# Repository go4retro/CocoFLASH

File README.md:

# CocoFLASH
Tandy Color Computer CocoFLASH

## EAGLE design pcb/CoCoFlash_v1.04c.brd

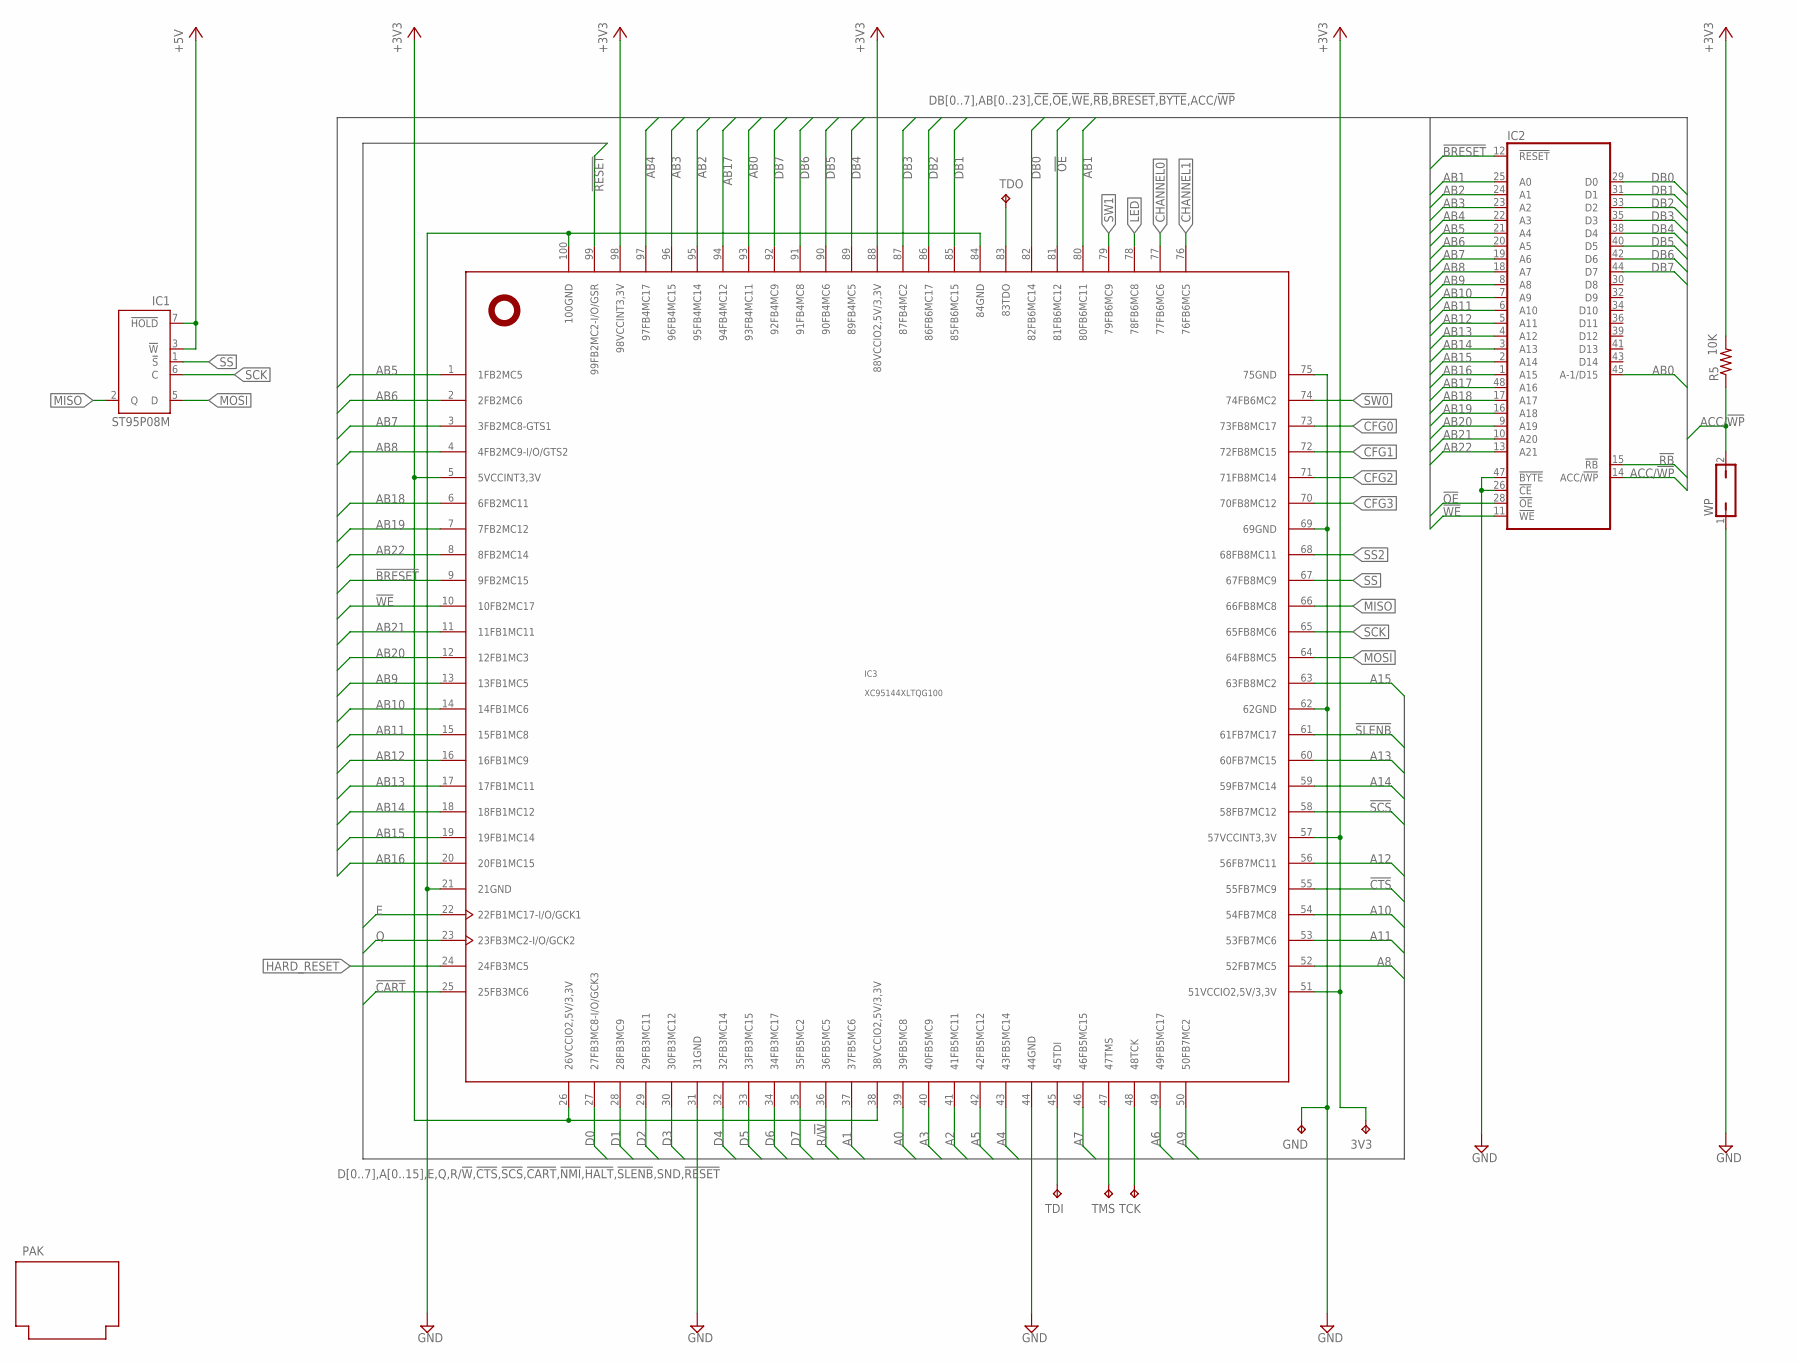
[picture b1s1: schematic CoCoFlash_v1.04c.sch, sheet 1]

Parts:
3V3: TPTP08R; TP08R
GND: TPTP08R; TP08R
IC1: ST95P08M; SO08
IC2: MX29LV640; TSOP48
IC3: XC95144XLTQG100; TQFP100
PAK: PROGRAM_PAK
R5: 10K; R0402
TCK: TPTP08R; TP08R
TDI: TPTP08R; TP08R
TDO: TPTP08R; TP08R
TMS: TPTP08R; TP08R
WP: JP1Q; JP1

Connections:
!BRESET: IC2.12 (!RESET), IC3.9 (9FB2MC15)
!CART: IC3.25 (25FB3MC6); also elsewhere on the board
!CTS: IC3.55 (55FB7MC9); also elsewhere on the board
!OE: IC2.28 (!OE), IC3.81 (81FB6MC12)
!RB: IC2.15 (!RB)
!RESET: IC3.99 (99FB2MC2-I/O/GSR); also elsewhere on the board
!SCS: IC3.58 (58FB7MC12); also elsewhere on the board
!SLENB: IC3.61 (61FB7MC17); also elsewhere on the board
!WE: IC2.11 (!WE), IC3.10 (10FB2MC17)
+3V3: 3V3.TP, IC3.5 (5VCCINT3,3V), IC3.26 (26VCCIO2,5V/3,3V), IC3.38 (38VCCIO2,5V/3,3V), IC3.51 (51VCCIO2,5V/3,3V), IC3.57 (57VCCINT3,3V), IC3.88 (88VCCIO2,5V/3,3V), IC3.98 (98VCCINT3,3V), R5.2; also elsewhere on the board
+5V: IC1.3 (!W), IC1.7 (!HOLD); also elsewhere on the board
A0: IC3.39 (39FB5MC8); also elsewhere on the board
A1: IC3.37 (37FB5MC6); also elsewhere on the board
A2: IC3.41 (41FB5MC11); also elsewhere on the board
A3: IC3.40 (40FB5MC9); also elsewhere on the board
A4: IC3.43 (43FB5MC14); also elsewhere on the board
A5: IC3.42 (42FB5MC12); also elsewhere on the board
A6: IC3.49 (49FB5MC17); also elsewhere on the board
A7: IC3.46 (46FB5MC15); also elsewhere on the board
A8: IC3.52 (52FB7MC5); also elsewhere on the board
A9: IC3.50 (50FB7MC2); also elsewhere on the board
A10: IC3.54 (54FB7MC8); also elsewhere on the board
A11: IC3.53 (53FB7MC6); also elsewhere on the board
A12: IC3.56 (56FB7MC11); also elsewhere on the board
A13: IC3.60 (60FB7MC15); also elsewhere on the board
A14: IC3.59 (59FB7MC14); also elsewhere on the board
A15: IC3.63 (63FB8MC2); also elsewhere on the board
AB0: IC2.45 (A-1/D15), IC3.93 (93FB4MC11)
AB1: IC2.25 (A0), IC3.80 (80FB6MC11)
AB2: IC2.24 (A1), IC3.95 (95FB4MC14)
AB3: IC2.23 (A2), IC3.96 (96FB4MC15)
AB4: IC2.22 (A3), IC3.97 (97FB4MC17)
AB5: IC2.21 (A4), IC3.1 (1FB2MC5)
AB6: IC2.20 (A5), IC3.2 (2FB2MC6)
AB7: IC2.19 (A6), IC3.3 (3FB2MC8-GTS1)
AB8: IC2.18 (A7), IC3.4 (4FB2MC9-I/O/GTS2)
AB9: IC2.8 (A8), IC3.13 (13FB1MC5)
AB10: IC2.7 (A9), IC3.14 (14FB1MC6)
AB11: IC2.6 (A10), IC3.15 (15FB1MC8)
AB12: IC2.5 (A11), IC3.16 (16FB1MC9)
AB13: IC2.4 (A12), IC3.17 (17FB1MC11)
AB14: IC2.3 (A13), IC3.18 (18FB1MC12)
AB15: IC2.2 (A14), IC3.19 (19FB1MC14)
AB16: IC2.1 (A15), IC3.20 (20FB1MC15)
AB17: IC2.48 (A16), IC3.94 (94FB4MC12)
AB18: IC2.17 (A17), IC3.6 (6FB2MC11)
AB19: IC2.16 (A18), IC3.7 (7FB2MC12)
AB20: IC2.9 (A19), IC3.12 (12FB1MC3)
AB21: IC2.10 (A20), IC3.11 (11FB1MC11)
AB22: IC2.13 (A21), IC3.8 (8FB2MC14)
ACC/!WP: IC2.14 (ACC/!WP), R5.1, WP.2
CFG0: IC3.73 (73FB8MC17); also elsewhere on the board
CFG1: IC3.72 (72FB8MC15); also elsewhere on the board
CFG2: IC3.71 (71FB8MC14); also elsewhere on the board
CFG3: IC3.70 (70FB8MC12); also elsewhere on the board
CHANNEL0: IC3.77 (77FB6MC6); also elsewhere on the board
CHANNEL1: IC3.76 (76FB6MC5); also elsewhere on the board
D0: IC3.27 (27FB3MC8-I/O/GCK3); also elsewhere on the board
D1: IC3.28 (28FB3MC9); also elsewhere on the board
D2: IC3.29 (29FB3MC11); also elsewhere on the board
D3: IC3.30 (30FB3MC12); also elsewhere on the board
D4: IC3.32 (32FB3MC14); also elsewhere on the board
D5: IC3.33 (33FB3MC15); also elsewhere on the board
D6: IC3.34 (34FB3MC17); also elsewhere on the board
D7: IC3.35 (35FB5MC2); also elsewhere on the board
DB0: IC2.29 (D0), IC3.82 (82FB6MC14)
DB1: IC2.31 (D1), IC3.85 (85FB6MC15)
DB2: IC2.33 (D2), IC3.86 (86FB6MC17)
DB3: IC2.35 (D3), IC3.87 (87FB4MC2)
DB4: IC2.38 (D4), IC3.89 (89FB4MC5)
DB5: IC2.40 (D5), IC3.90 (90FB4MC6)
DB6: IC2.42 (D6), IC3.91 (91FB4MC8)
DB7: IC2.44 (D7), IC3.92 (92FB4MC9)
E: IC3.22 (22FB1MC17-I/O/GCK1); also elsewhere on the board
GND: GND.TP, IC2.26 (!CE), IC2.47 (!BYTE), IC3.21 (21GND), IC3.31 (31GND), IC3.44 (44GND), IC3.62 (62GND), IC3.69 (69GND), IC3.75 (75GND), IC3.84 (84GND), IC3.100 (100GND), WP.1; also elsewhere on the board
HARD_RESET: IC3.24 (24FB3MC5); also elsewhere on the board
LED: IC3.78 (78FB6MC8); also elsewhere on the board
MISO: IC1.2 (Q), IC3.66 (66FB8MC8)
MOSI: IC1.5 (D), IC3.64 (64FB8MC5)
unnamed: IC3.45 (45TDI), TDI.TP
unnamed: IC3.47 (47TMS), TMS.TP
unnamed: IC3.48 (48TCK), TCK.TP
unnamed: IC3.83 (83TDO), TDO.TP
Q: IC3.23 (23FB3MC2-I/O/GCK2); also elsewhere on the board
R/!W: IC3.36 (36FB5MC5); also elsewhere on the board
SCK: IC1.6 (C), IC3.65 (65FB8MC6)
SS: IC1.1 (!S), IC3.67 (67FB8MC9)
SS2: IC3.68 (68FB8MC11)
SW0: IC3.74 (74FB6MC2); also elsewhere on the board
SW1: IC3.79 (79FB6MC9); also elsewhere on the board

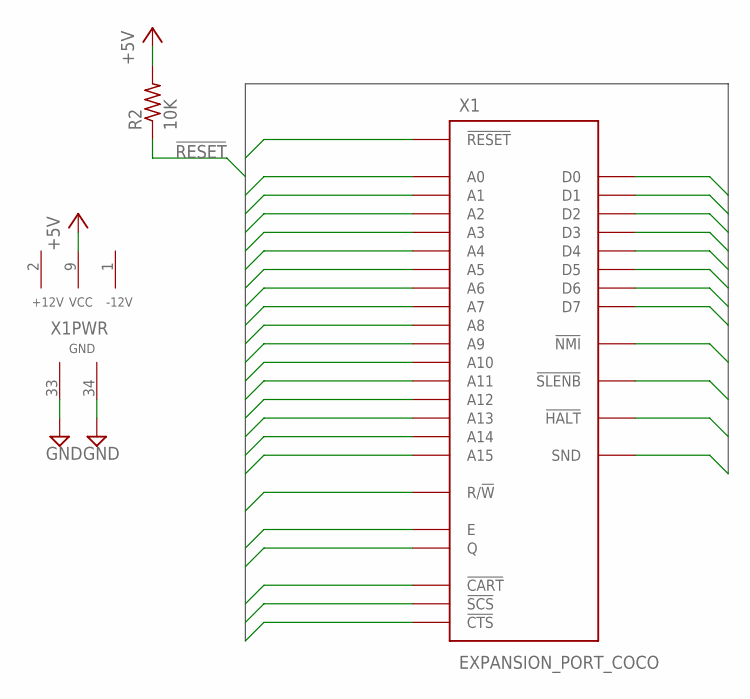
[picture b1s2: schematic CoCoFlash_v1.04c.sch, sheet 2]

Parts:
R2: 10K; R0402
X1: EXPANSION_PORT_COCO; MA20-2

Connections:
!CART: X1.8 (!CART); also elsewhere on the board
!CTS: X1.32 (!CTS); also elsewhere on the board
!HALT: X1.3 (!HALT)
!NMI: X1.4 (!NMI)
!RESET: R2.1, X1.5 (!RESET); also elsewhere on the board
!SCS: X1.36 (!SCS); also elsewhere on the board
!SLENB: X1.40 (!SLENB); also elsewhere on the board
+5V: R2.2, X1.9 (VCC); also elsewhere on the board
+12V: X1.2 (+12V)
-12V: X1.1 (-12V)
A0: X1.19 (A0); also elsewhere on the board
A1: X1.20 (A1); also elsewhere on the board
A2: X1.21 (A2); also elsewhere on the board
A3: X1.22 (A3); also elsewhere on the board
A4: X1.23 (A4); also elsewhere on the board
A5: X1.24 (A5); also elsewhere on the board
A6: X1.25 (A6); also elsewhere on the board
A7: X1.26 (A7); also elsewhere on the board
A8: X1.27 (A8); also elsewhere on the board
A9: X1.28 (A9); also elsewhere on the board
A10: X1.29 (A10); also elsewhere on the board
A11: X1.30 (A11); also elsewhere on the board
A12: X1.31 (A12); also elsewhere on the board
A13: X1.37 (A13); also elsewhere on the board
A14: X1.38 (A14); also elsewhere on the board
A15: X1.39 (A15); also elsewhere on the board
D0: X1.10 (D0); also elsewhere on the board
D1: X1.11 (D1); also elsewhere on the board
D2: X1.12 (D2); also elsewhere on the board
D3: X1.13 (D3); also elsewhere on the board
D4: X1.14 (D4); also elsewhere on the board
D5: X1.15 (D5); also elsewhere on the board
D6: X1.16 (D6); also elsewhere on the board
D7: X1.17 (D7); also elsewhere on the board
E: X1.6 (E); also elsewhere on the board
GND: X1.33 (GND), X1.34 (GND); also elsewhere on the board
Q: X1.7 (Q); also elsewhere on the board
R/!W: X1.18 (R/!W); also elsewhere on the board
SND: X1.35 (SND); also elsewhere on the board

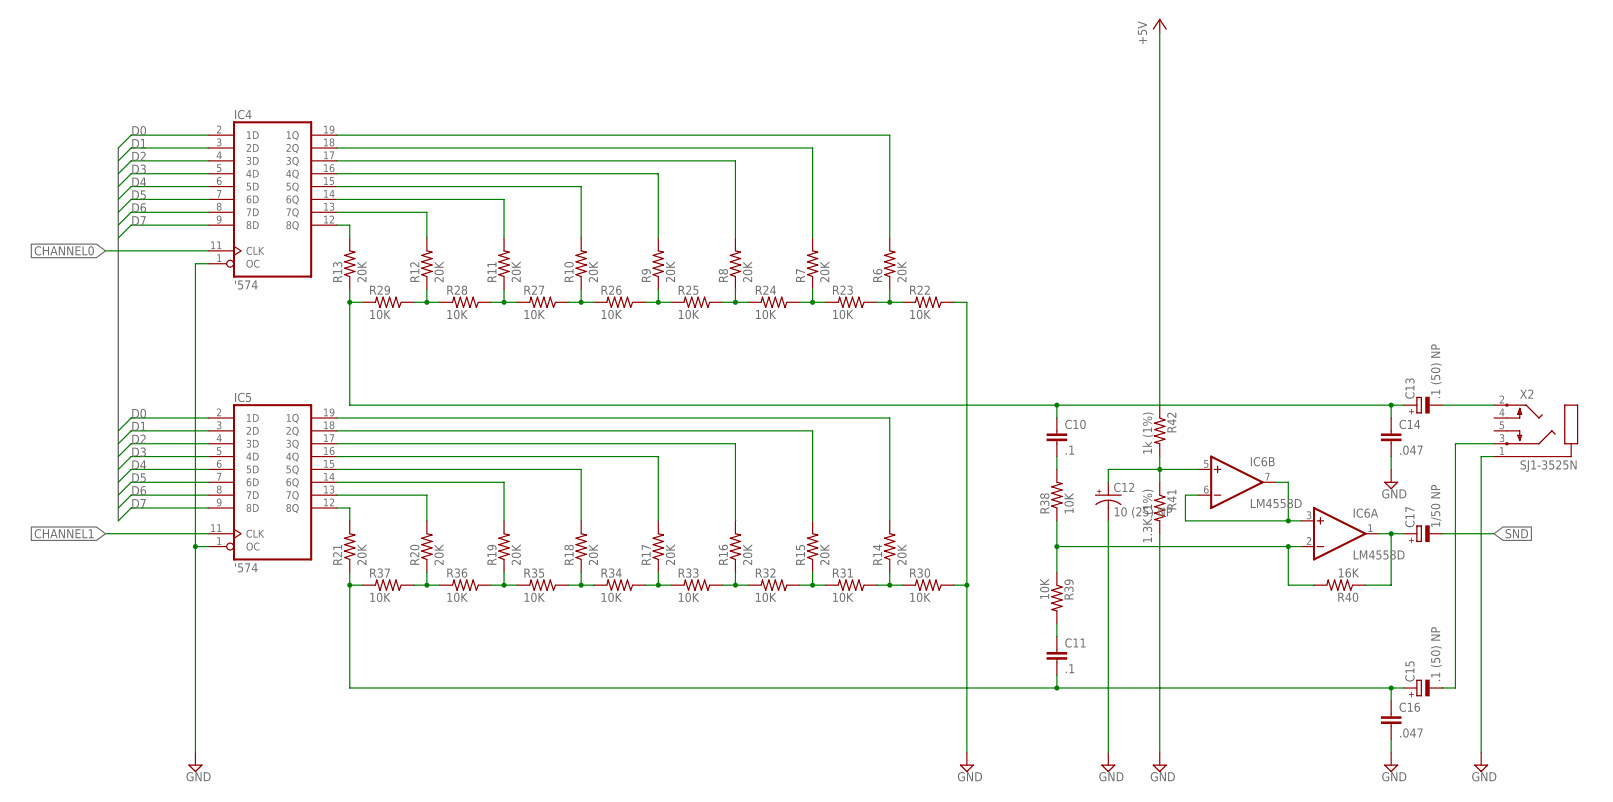
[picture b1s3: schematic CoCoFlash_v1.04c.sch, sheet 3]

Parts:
C10, C11: .1; C050-025X075
C12: 10 (25) NP; E1,8-4
C13, C15: .1 (50) NP; E1,8-4
C14, C16: .047; C050-025X075
C17: 1/50 NP; E1,8-4
IC4, IC5: '574; TSSOP20
IC6: LM4558D; SO08
R6, R7, R8, R9, R10, R11, R12, R13, R14, R15, R16, R17, R18, R19, R20, R21: 20K; R1206
R22, R23, R24, R25, R26, R27, R28, R29, R30, R31, R32, R33, R34, R35, R36, R37, R38, R39: 10K; R1206
R40: 16K; R1206
R41: 1.3K (1%); R0402
R42: 1k (1%); R0402
X2: SJ1-3525N

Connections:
+5V: R42.1; also elsewhere on the board
CHANNEL0: IC4.11 (CLK); also elsewhere on the board
CHANNEL1: IC5.11 (CLK); also elsewhere on the board
D0: IC4.2 (1D), IC5.2 (1D); also elsewhere on the board
D1: IC4.3 (2D), IC5.3 (2D); also elsewhere on the board
D2: IC4.4 (3D), IC5.4 (3D); also elsewhere on the board
D3: IC4.5 (4D), IC5.5 (4D); also elsewhere on the board
D4: IC4.6 (5D), IC5.6 (5D); also elsewhere on the board
D5: IC4.7 (6D), IC5.7 (6D); also elsewhere on the board
D6: IC4.8 (7D), IC5.8 (7D); also elsewhere on the board
D7: IC4.9 (8D), IC5.9 (8D); also elsewhere on the board
GND: C12.-, C14.2, C16.2, IC4.1 (OC), IC5.1 (OC), R22.1, R30.1, R41.2, X2.1; also elsewhere on the board
unnamed: IC4.18 (2Q), R7.2
unnamed: R6.1, R22.2, R23.1
unnamed: C15.-, X2.3
unnamed: IC4.19 (1Q), R6.2
unnamed: C13.-, X2.2
unnamed: IC4.17 (3Q), R8.2
unnamed: IC4.16 (4Q), R9.2
unnamed: IC4.15 (5Q), R10.2
unnamed: IC4.14 (6Q), R11.2
unnamed: IC4.13 (7Q), R12.2
unnamed: IC4.12 (8Q), R13.2
unnamed: R7.1, R23.2, R24.1
unnamed: R8.1, R24.2, R25.1
unnamed: R9.1, R25.2, R26.1
unnamed: R10.1, R26.2, R27.1
unnamed: R11.1, R27.2, R28.1
unnamed: R12.1, R28.2, R29.1
unnamed: C10.1, C13.+, C14.1, R13.1, R29.2
unnamed: IC5.19 (1Q), R14.2
unnamed: IC5.18 (2Q), R15.2
unnamed: IC5.17 (3Q), R16.2
unnamed: IC5.16 (4Q), R17.2
unnamed: IC5.15 (5Q), R18.2
unnamed: IC5.14 (6Q), R19.2
unnamed: IC5.13 (7Q), R20.2
unnamed: IC5.12 (8Q), R21.2
unnamed: C11.2, C15.+, C16.1, R21.1, R37.2
unnamed: R20.1, R36.2, R37.1
unnamed: R19.1, R35.2, R36.1
unnamed: R18.1, R34.2, R35.1
unnamed: R17.1, R33.2, R34.1
unnamed: R16.1, R32.2, R33.1
unnamed: R15.1, R31.2, R32.1
unnamed: R14.1, R30.2, R31.1
unnamed: C10.2, R38.2
unnamed: C11.1, R39.2
unnamed: IC6.2 (-IN), R38.1, R39.1, R40.2
unnamed: IC6.3 (+IN), IC6.6 (-IN), IC6.7 (OUT)
unnamed: C17.+, IC6.1 (OUT), R40.1
unnamed: C12.+, IC6.5 (+IN), R41.1, R42.2
SND: C17.-; also elsewhere on the board

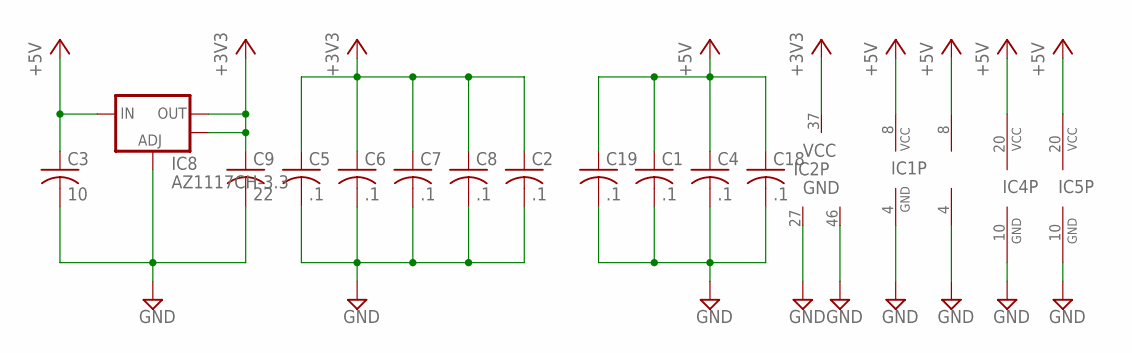
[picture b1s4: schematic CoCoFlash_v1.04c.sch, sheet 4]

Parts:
C1, C2, C4, C5, C6, C7, C8, C18, C19: .1; C0402
C3: 10; C0805
C9: 22; C0805
IC1: ST95P08M; SO08
IC2: MX29LV640; TSOP48
IC4, IC5: '574; TSSOP20
IC6: LM4558D; SO08
IC8: AZ1117CH-3.3; SOT223

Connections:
+3V3: C2.1, C5.1, C6.1, C7.1, C8.1, C9.1, IC2.37 (VCC), IC8.2 (OUT), IC8.4 (OUT); also elsewhere on the board
+5V: C1.1, C3.1, C4.1, C18.1, C19.1, IC1.8 (VCC), IC4.20 (VCC), IC5.20 (VCC), IC6.8 (V+), IC8.3 (IN); also elsewhere on the board
GND: C1.2, C2.2, C3.2, C4.2, C5.2, C6.2, C7.2, C8.2, C9.2, C18.2, C19.2, IC1.4 (GND), IC2.27 (GND), IC2.46 (GND), IC4.10 (GND), IC5.10 (GND), IC6.4 (V-), IC8.1 (ADJ); also elsewhere on the board

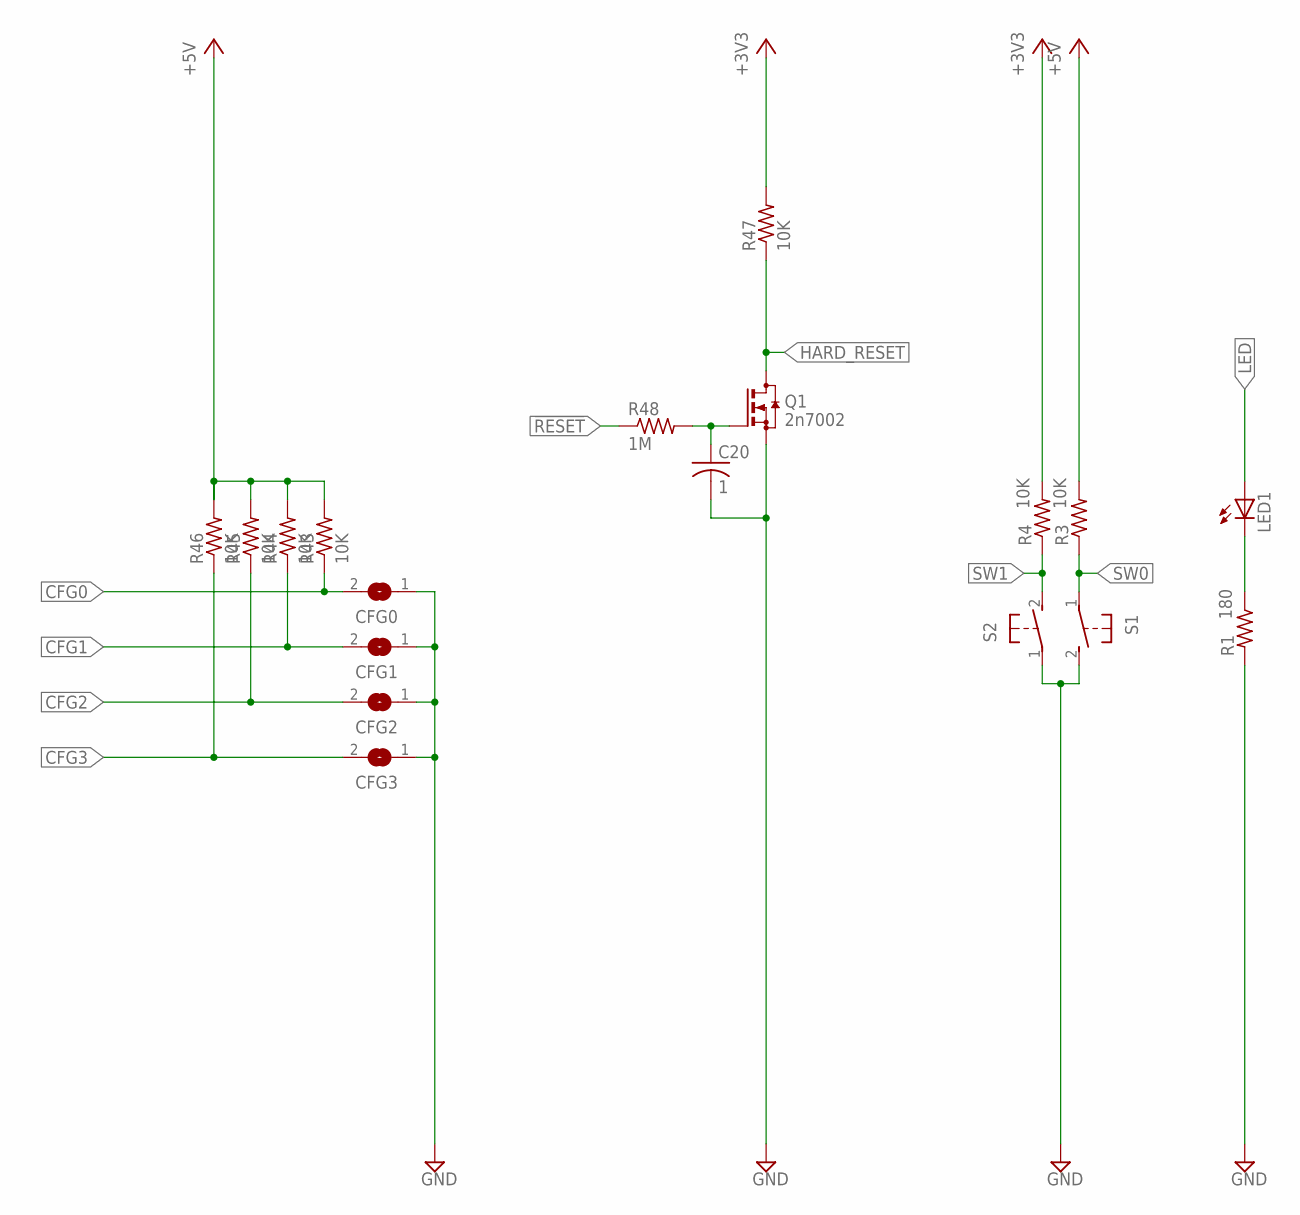
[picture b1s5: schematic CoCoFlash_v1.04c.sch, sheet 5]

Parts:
C20: 1; C0402
CFG0, CFG1, CFG2, CFG3: SJ
LED1: LED3MM
Q1: 2n7002; SOT23
R1: 180; R0402
R3, R4, R43, R44, R45, R46, R47: 10K; R0402
R48: 1M; R0402
S1, S2: 31-XX; B3F-31XX

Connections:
!RESET: R48.1; also elsewhere on the board
+3V1: C20.1, Q1.1 (G), R48.2
+3V3: R4.2, R47.2; also elsewhere on the board
+5V: R3.2, R43.2, R44.2, R45.2, R46.2; also elsewhere on the board
CFG0: CFG0.2, R43.1; also elsewhere on the board
CFG1: CFG1.2, R44.1; also elsewhere on the board
CFG2: CFG2.2, R45.1; also elsewhere on the board
CFG3: CFG3.2, R46.1; also elsewhere on the board
GND: C20.2, CFG0.1, CFG1.1, CFG2.1, CFG3.1, Q1.2 (S), R1.2, S1.2 (S), S2.1; also elsewhere on the board
HARD_RESET: Q1.3 (D), R47.1; also elsewhere on the board
LED: LED1.A; also elsewhere on the board
unnamed: LED1.K (C), R1.1
SW0: R3.1, S1.1; also elsewhere on the board
SW1: R4.1, S2.2 (S); also elsewhere on the board

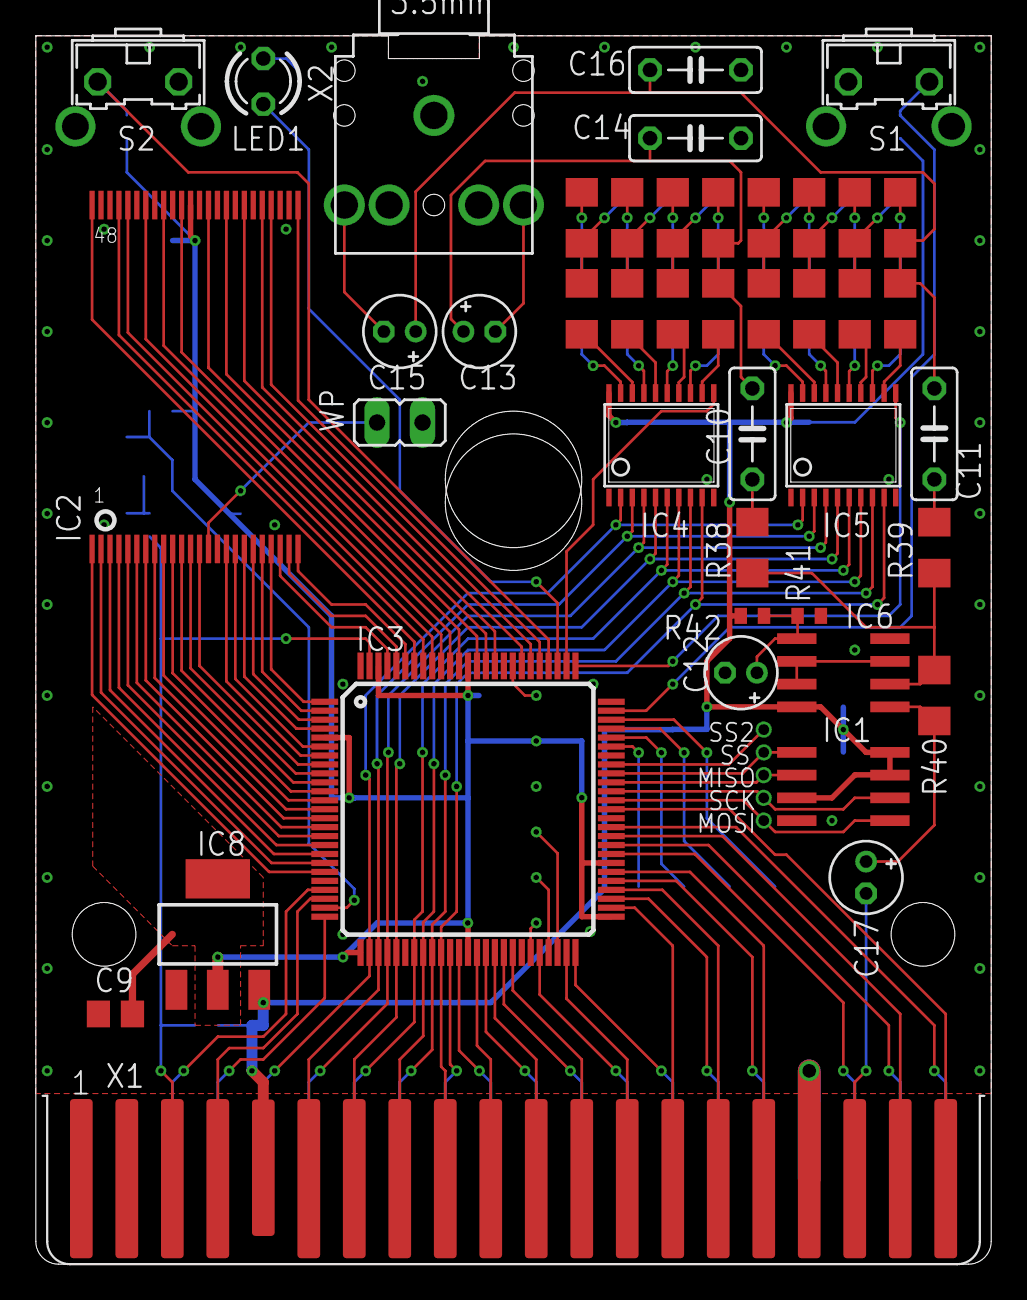
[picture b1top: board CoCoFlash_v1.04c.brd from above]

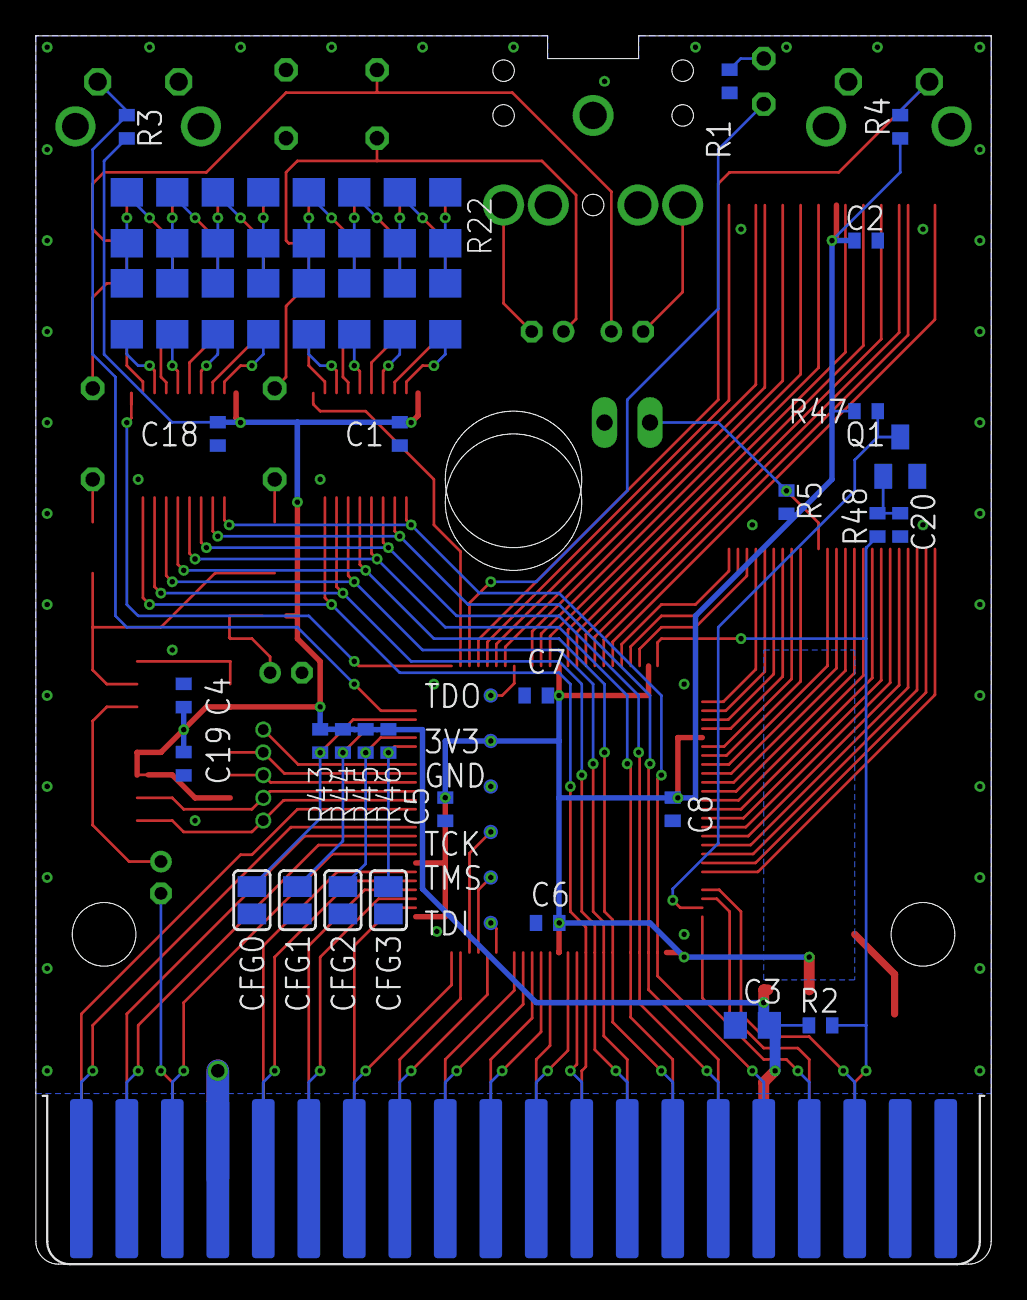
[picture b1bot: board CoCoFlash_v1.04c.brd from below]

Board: 2 copper layers, 53.3 x 68.6 mm, 93 parts (49 on the bottom side), 131 nets.

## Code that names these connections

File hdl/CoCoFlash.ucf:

#PACE: Start of Constraints generated by PACE

#PACE: Start of PACE I/O Pin Assignments
NET "_cart"  LOC = "P25"  ; 
NET "_channel<0>"  LOC = "P76"  ;
NET "_channel<1>"  LOC = "P77"  ;
NET "_cts"  LOC = "P55"  ; 
NET "_freset"  LOC = "P9"  ; 
NET "_oe"  LOC = "P81"  ; 
NET "_reset"  LOC = "P99"  ; 
NET "_scs"  LOC = "P58"  ; 
NET "_slenb"  LOC = "P61"  ; 
NET "_ss"  LOC = "P67"  ; 
NET "_ss2"  LOC = "P68"  ; 
NET "_we"  LOC = "P10"  ; 
NET "address<0>"  LOC = "P39"  ; 
NET "address<10>"  LOC = "P54"  ; 
NET "address<11>"  LOC = "P53"  ; 
NET "address<12>"  LOC = "P56"  ; 
NET "address<13>"  LOC = "P60"  ; 
NET "address<14>"  LOC = "P59"  ; 
NET "address<15>"  LOC = "P63"  ; 
NET "address<1>"  LOC = "P37"  ; 
NET "address<2>"  LOC = "P41"  ; 
NET "address<3>"  LOC = "P40"  ; 
NET "address<4>"  LOC = "P43"  ; 
NET "address<5>"  LOC = "P42"  ; 
NET "address<6>"  LOC = "P49"  ; 
NET "address<7>"  LOC = "P46"  ; 
NET "address<8>"  LOC = "P52"  ; 
NET "address<9>"  LOC = "P50"  ; 
NET "baddress<0>"  LOC = "P93"  ; 
NET "baddress<10>"  LOC = "P14"  ; 
NET "baddress<11>"  LOC = "P15"  ; 
NET "baddress<12>"  LOC = "P16"  ; 
NET "baddress<13>"  LOC = "P17"  ; 
NET "baddress<14>"  LOC = "P18"  ; 
NET "baddress<15>"  LOC = "P19"  ; 
NET "baddress<16>"  LOC = "P20"  ; 
NET "baddress<17>"  LOC = "P94"  ; 
NET "baddress<18>"  LOC = "P6"  ; 
NET "baddress<19>"  LOC = "P7"  ; 
NET "baddress<1>"  LOC = "P80"  ; 
NET "baddress<20>"  LOC = "P12"  ; 
NET "baddress<21>"  LOC = "P11"  ; 
NET "baddress<22>"  LOC = "P8"  ; 
NET "baddress<2>"  LOC = "P95"  ; 
NET "baddress<3>"  LOC = "P96"  ; 
NET "baddress<4>"  LOC = "P97"  ; 
NET "baddress<5>"  LOC = "P1"  ; 
NET "baddress<6>"  LOC = "P2"  ; 
NET "baddress<7>"  LOC = "P3"  ; 
NET "baddress<8>"  LOC = "P4"  ; 
NET "baddress<9>"  LOC = "P13"  ; 
NET "bdata<0>"  LOC = "P82"  ; 
NET "bdata<1>"  LOC = "P85"  ; 
NET "bdata<2>"  LOC = "P86"  ; 
NET "bdata<3>"  LOC = "P87"  ; 
NET "bdata<4>"  LOC = "P89"  ; 
NET "bdata<5>"  LOC = "P90"  ; 
NET "bdata<6>"  LOC = "P91"  ; 
NET "bdata<7>"  LOC = "P92"  ; 
NET "cfg<0>"  LOC = "P73"  ; 
NET "cfg<1>"  LOC = "P72"  ; 
NET "cfg<2>"  LOC = "P71"  ; 
NET "cfg<3>"  LOC = "P70"  ; 
NET "data<0>"  LOC = "P27"  ; 
NET "data<1>"  LOC = "P28"  ; 
NET "data<2>"  LOC = "P29"  ; 
NET "data<3>"  LOC = "P30"  ; 
NET "data<4>"  LOC = "P32"  ; 
NET "data<5>"  LOC = "P33"  ; 
NET "data<6>"  LOC = "P34"  ; 
NET "data<7>"  LOC = "P35"  ; 
NET "e"  LOC = "P22"  ; 
NET "led"  LOC = "P78"  ; 
NET "miso"  LOC = "P66"  ; 
NET "mosi"  LOC = "P64"  ; 
NET "q"  LOC = "P23"  ; 
NET "r_w"  LOC = "P36"  ; 
NET "reset_long"  LOC = "P24"  ; 
NET "sck"  LOC = "P65"  ; 
NET "switch<0>"  LOC = "P74"  ; 
NET "switch<1>"  LOC = "P79"  ; 

#PACE: Start of PACE Area Constraints

#PACE: Start of PACE Prohibit Constraints

#PACE: End of Constraints generated by PACE

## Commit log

2017-07-12 Rietveld Rietveld rietveldh@hotmail.com updated menu
2017-07-12 Add HDL Project
2018-02-21 General updates
2018-02-22 Add Pere Serrat's Dragon Apps
2018-03-11 Updated license
2019-05-21 Small PCB cleanup

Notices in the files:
parts and their libraries:
SparkFun: Licensing: CC v3.0 Share-Alike You are welcome to use this library for commercial purposes.
